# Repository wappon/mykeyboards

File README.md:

### wappon

e-mail:hetiantamo@gmail.com

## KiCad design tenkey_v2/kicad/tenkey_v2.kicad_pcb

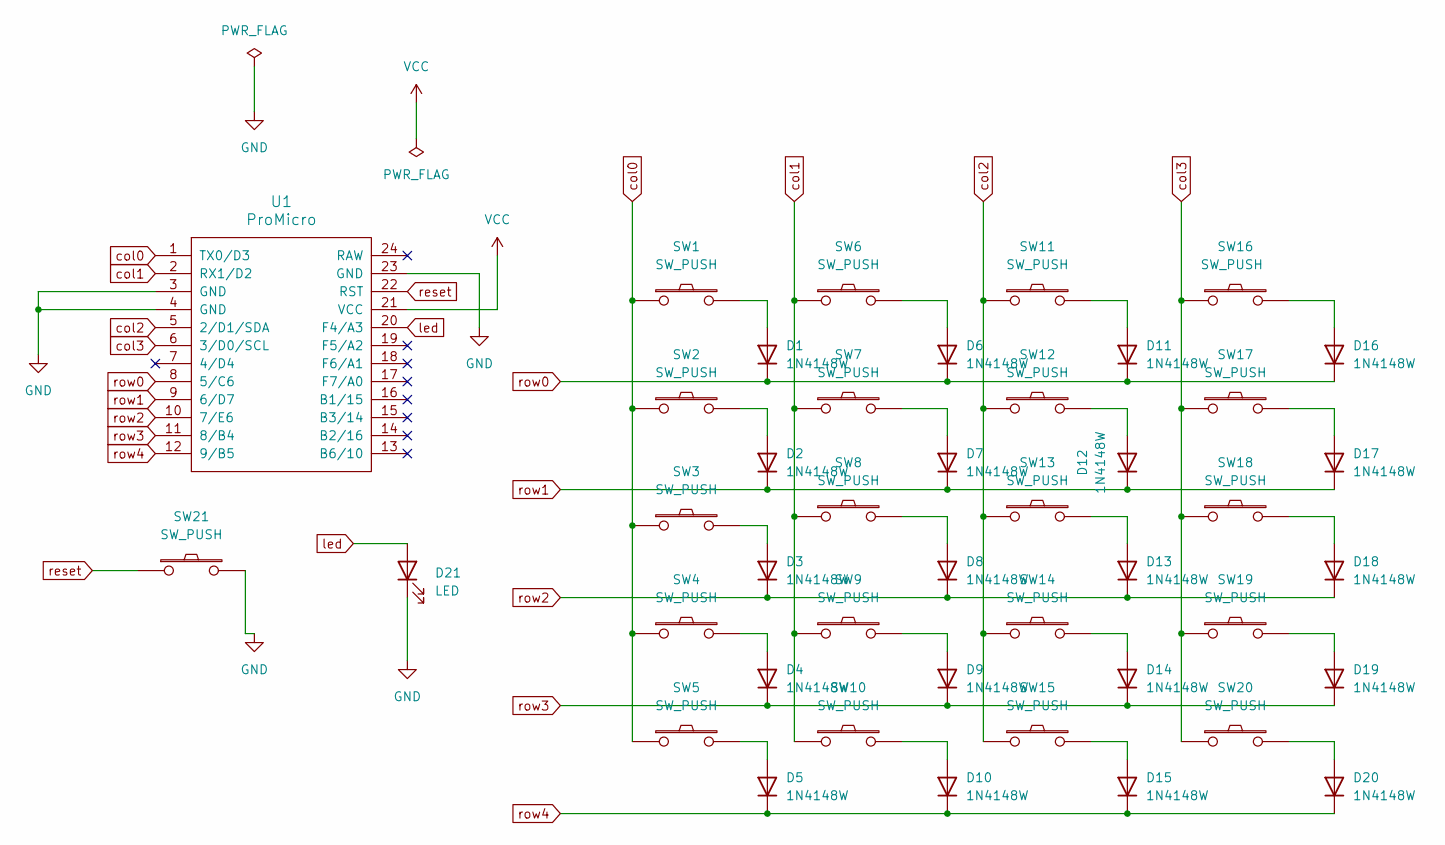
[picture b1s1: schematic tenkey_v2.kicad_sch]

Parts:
D1, D2, D3, D4, D5, D6, D7, D8, D9, D10, D11, D12, D13, D14, D15, D16, D17, D18, D19, D20: 1N4148W; D_SOD-123
D21: LED; LED_D3.0mm
SW1, SW2, SW3, SW4, SW5, SW6, SW7, SW8, SW9, SW10, SW11, SW12, SW13, SW14, SW15, SW16, SW17, SW18, SW19, SW20: SW_PUSH; SW_Cherry_MX_1.00u_PCB
SW21: SW_PUSH; ResetSW
U1: ProMicro; ArduinoProMicro

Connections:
GND: D21.1 (K), SW21.2, U1.3 (GND), U1.4 (GND), U1.23 (GND)
unnamed: D1.2 (A), SW1.2
unnamed: D2.2 (A), SW2.2
unnamed: D3.2 (A), SW3.2
unnamed: D4.2 (A), SW4.2
unnamed: D5.2 (A), SW5.2
unnamed: D6.2 (A), SW6.2
unnamed: D7.2 (A), SW7.2
unnamed: D8.2 (A), SW8.2
unnamed: D9.2 (A), SW9.2
unnamed: D10.2 (A), SW10.2
unnamed: D11.2 (A), SW11.2
unnamed: D12.2 (A), SW12.2
unnamed: D13.2 (A), SW13.2
unnamed: D14.2 (A), SW14.2
unnamed: D15.2 (A), SW15.2
unnamed: D16.2 (A), SW16.2
unnamed: D17.2 (A), SW17.2
unnamed: D18.2 (A), SW18.2
unnamed: D19.2 (A), SW19.2
unnamed: D20.2 (A), SW20.2
VCC: U1.21 (VCC)
col0: SW1.1, SW2.1, SW3.1, SW4.1, SW5.1, U1.1 (TX0/D3)
col1: SW6.1, SW7.1, SW8.1, SW9.1, SW10.1, U1.2 (RX1/D2)
col2: SW11.1, SW12.1, SW13.1, SW14.1, SW15.1, U1.5 (2/D1/SDA)
col3: SW16.1, SW17.1, SW18.1, SW19.1, SW20.1, U1.6 (3/D0/SCL)
led: D21.2 (A), U1.20 (F4/A3)
reset: SW21.1, U1.22 (RST)
row0: D1.1 (K), D6.1 (K), D11.1 (K), D16.1 (K), U1.8 (5/C6)
row1: D2.1 (K), D7.1 (K), D12.1 (K), D17.1 (K), U1.9 (6/D7)
row2: D3.1 (K), D8.1 (K), D13.1 (K), D18.1 (K), U1.10 (7/E6)
row3: D4.1 (K), D9.1 (K), D14.1 (K), D19.1 (K), U1.11 (8/B4)
row4: D5.1 (K), D10.1 (K), D15.1 (K), D20.1 (K), U1.12 (9/B5)

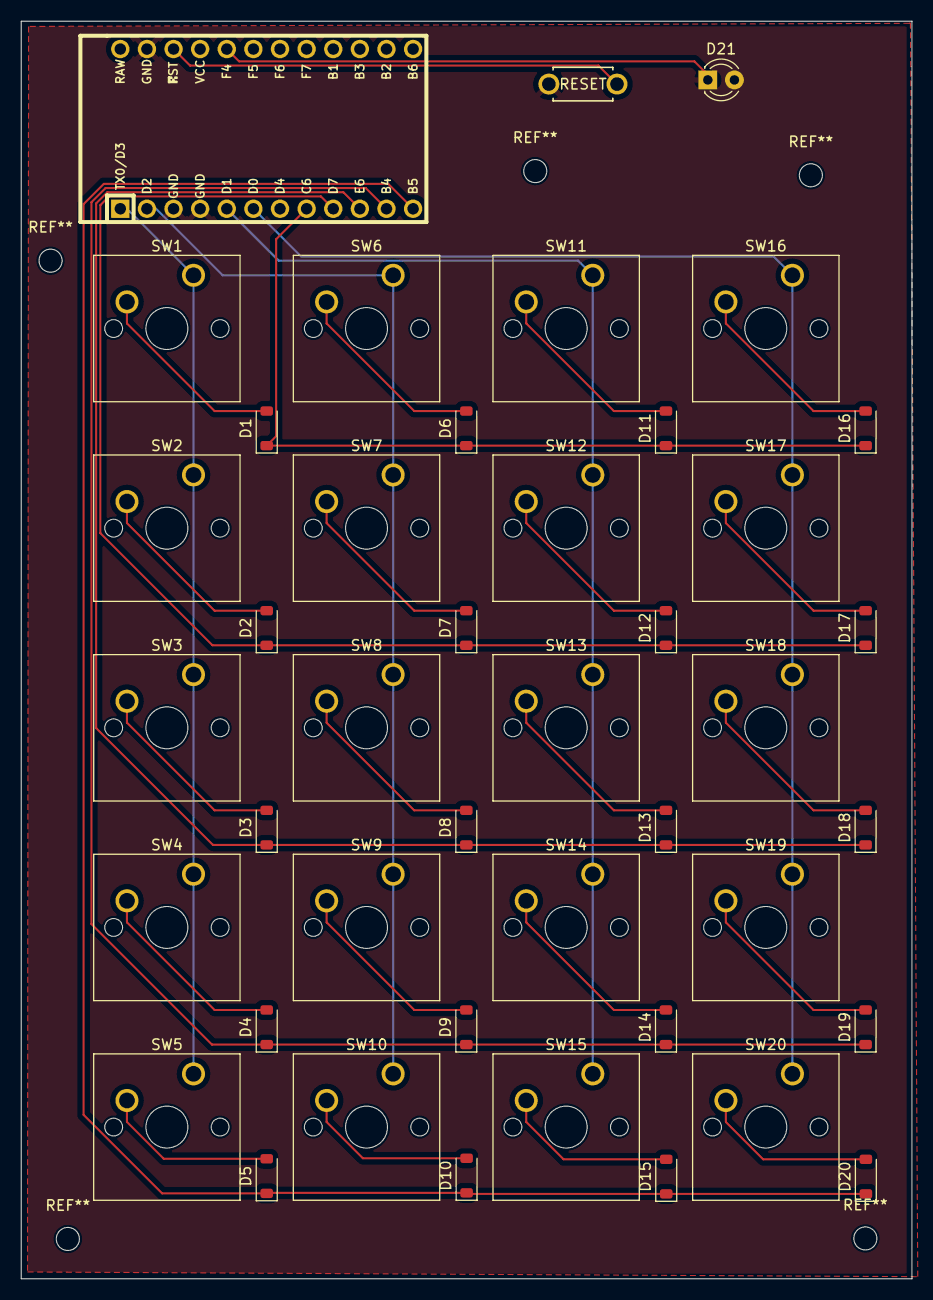
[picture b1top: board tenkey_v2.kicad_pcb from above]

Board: 2 copper layers, 85.0 x 120.0 mm, 43 parts (0 on the bottom side), 32 nets.

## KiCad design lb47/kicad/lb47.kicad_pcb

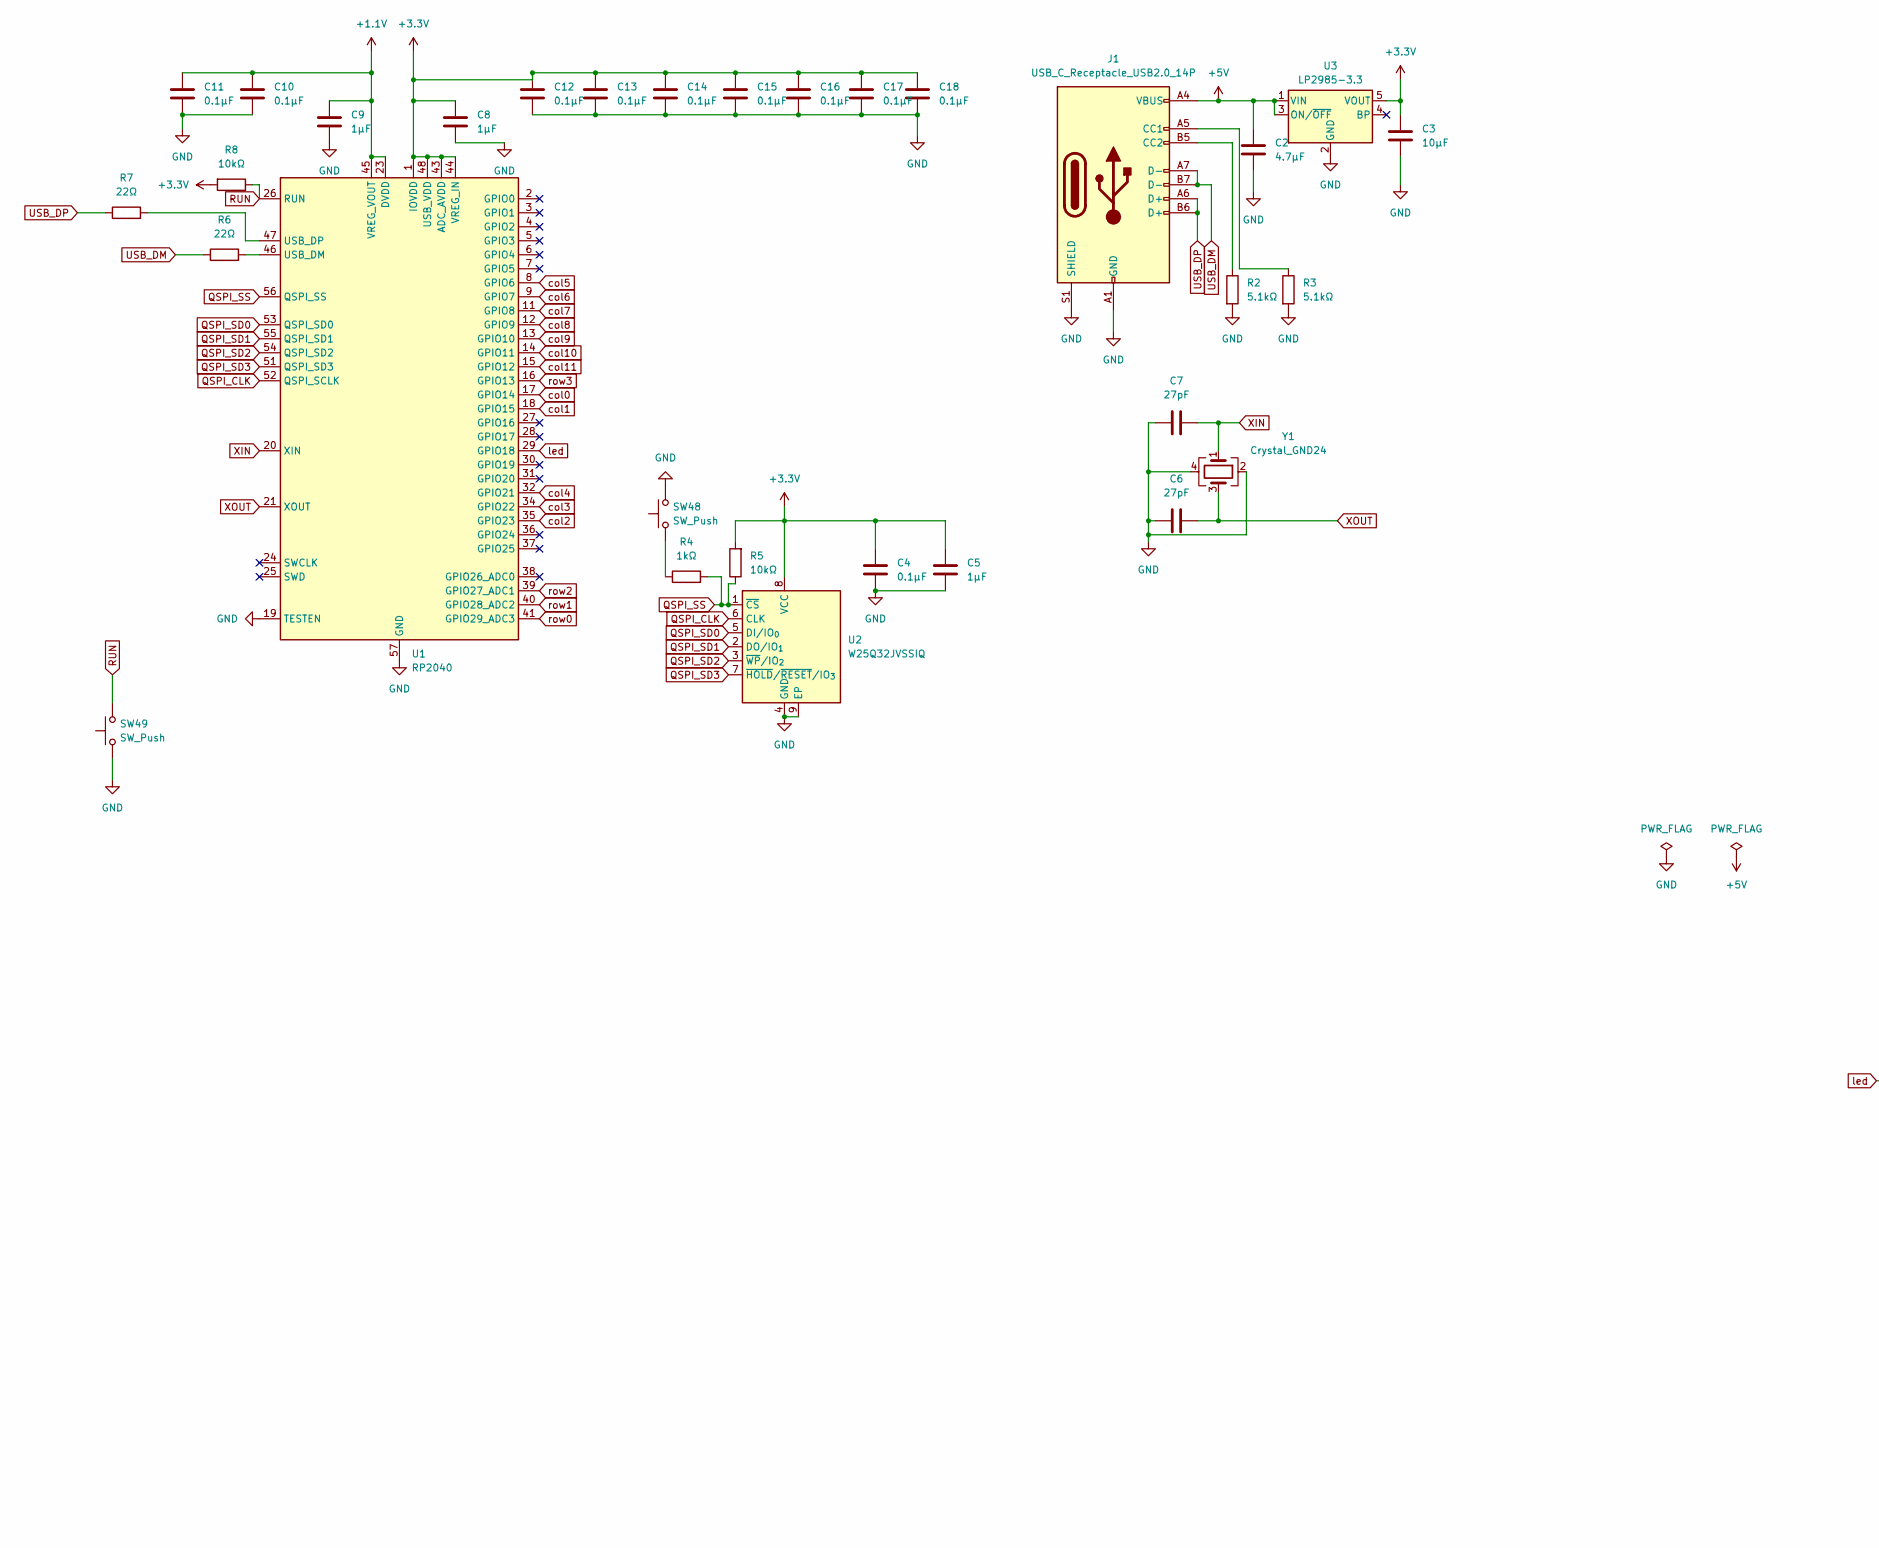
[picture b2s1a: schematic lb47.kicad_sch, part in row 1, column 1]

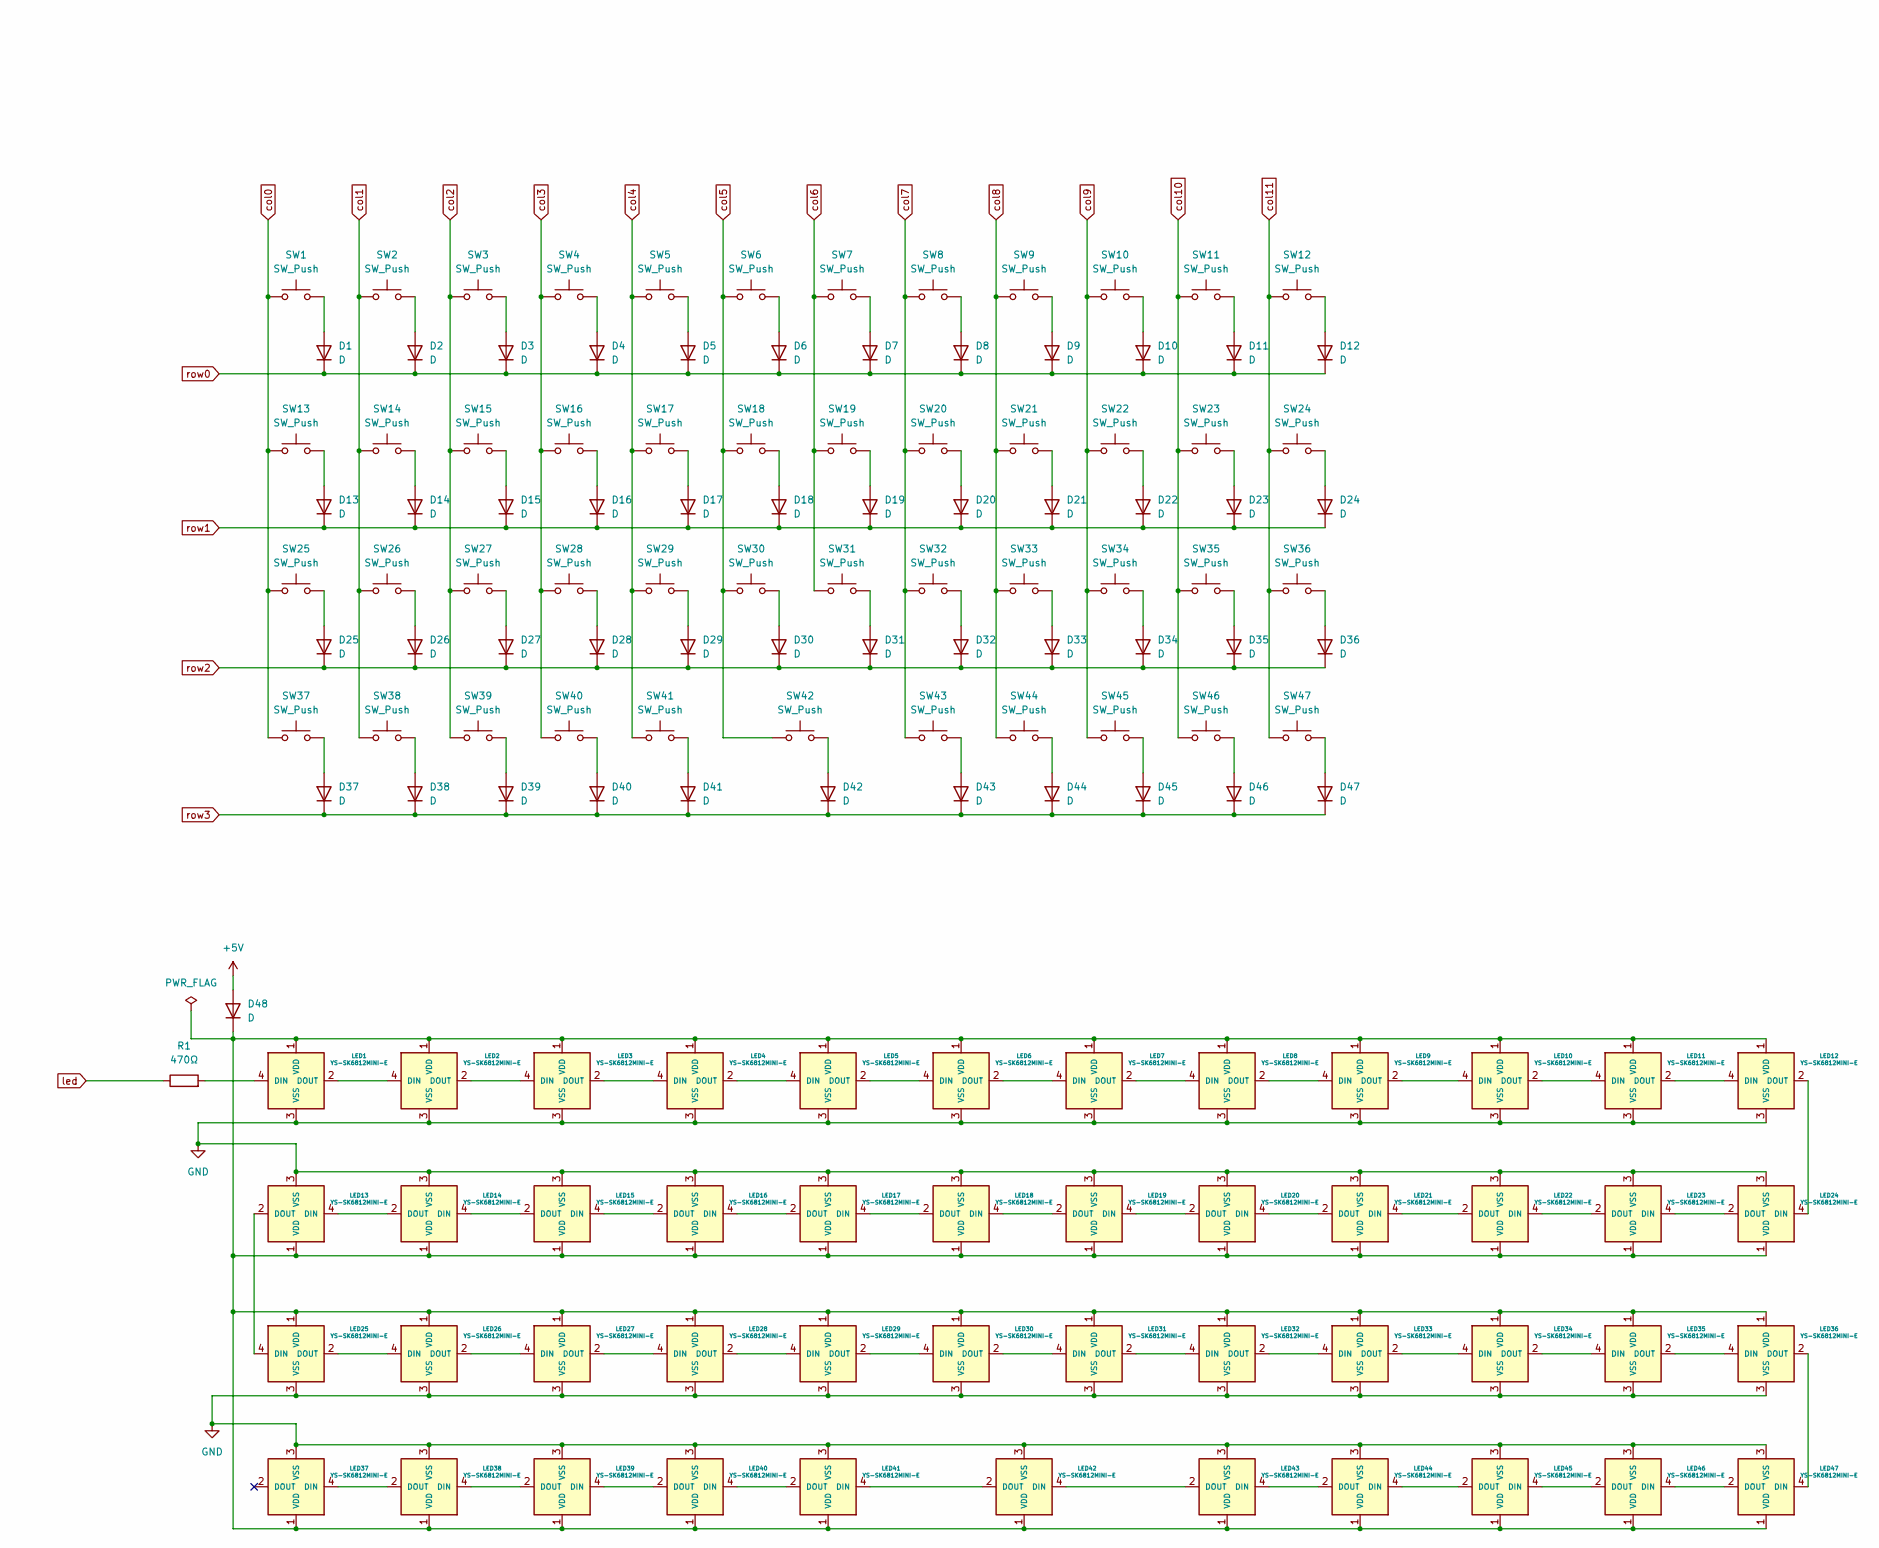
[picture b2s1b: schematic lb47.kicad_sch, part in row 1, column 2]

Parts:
C2: 4.7μF; C_0402_1005Metric; LCSC C335103
C3: 10μF; C_0402_1005Metric; LCSC C25054
C4, C10, C11, C12, C13, C14, C15, C16, C17, C18: 0.1μF; C_0402_1005Metric; LCSC C1525
C5, C8, C9: 1μF; C_0402_1005Metric; LCSC C14445
C6, C7: 27pF; C_0402_1005Metric; LCSC C1557
D1, D2, D3, D4, D5, D6, D7, D8, D9, D10, D11, D12, D13, D14, D15, D16, D17, D18, D19, D20, D21, D22, D23, D24, D25, D26, D27, D28, D29, D30, D31, D32, D33, D34, D35, D36, D37, D38, D39, D40, D41, D42, D43, D44, D45, D46, D47, D48: D; D_SOD-523; LCSC C27748
J1: USB_C_Receptacle_USB2.0_14P; USB_C_Receptacle_HRO_TYPE-C-31-M-12; LCSC C393939
LED1, LED2, LED3, LED4, LED5, LED6, LED7, LED8, LED9, LED10, LED11, LED12, LED13, LED14, LED15, LED16, LED17, LED18, LED19, LED20, LED21, LED22, LED23, LED24, LED25, LED26, LED27, LED28, LED29, LED30, LED31, LED32, LED33, LED34, LED35, LED36, LED37, LED38, LED39, LED40, LED41, LED42, LED43, LED44, LED45, LED46, LED47: YS-SK6812MINI-E; LCSC C5149201
R1: 470Ω; R_0402_1005Metric; LCSC C25117
R2, R3: 5.1kΩ; R_0402_1005Metric; LCSC C25905
R4: 1kΩ; R_0402_1005Metric; LCSC C11702
R5, R8: 10kΩ; R_0402_1005Metric; LCSC C25531
R6, R7: 22Ω; R_0402_1005Metric; LCSC C25092
SW1, SW2, SW3, SW4, SW5, SW6, SW7, SW8, SW9, SW10, SW11, SW12, SW13, SW14, SW15, SW16, SW17, SW18, SW19, SW20, SW21, SW22, SW23, SW24, SW25, SW26, SW27, SW28, SW29, SW30, SW31, SW32, SW33, SW34, SW35, SW36, SW37, SW38, SW39, SW40, SW41, SW42, SW43, SW44, SW45, SW46, SW47: SW_Push; CherryMX_Hotswap_1u
SW48, SW49: SW_Push; TSA017A2530B_C2888436; LCSC C589191
U1: RP2040; QFN-56-1EP_7x7mm_P0.4mm_EP3.2x3.2mm; LCSC C2040
U2: W25Q32JVSSIQ; WSON-8-1EP_8x6mm_P1.27mm_EP3.4x4.3mm; LCSC C82344
U3: LP2985-3.3; SOT-23-5; LCSC C95414
Y1: Crystal_GND24; Crystal_SMD_3225-4Pin_3.2x2.5mm; LCSC C403945

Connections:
+1.1V: C9.1, C10.1, C11.1, U1.23 (DVDD), U1.45 (VREG_VOUT), U1.50 (DVDD)
+3.3V: C3.1, C4.1, C5.1, C8.1, C12.1, C13.1, C14.1, C15.1, C16.1, C17.1, C18.1, R5.2, R8.2, U1.1 (IOVDD), U1.10 (IOVDD), U1.22 (IOVDD), U1.33 (IOVDD), U1.42 (IOVDD), U1.43 (ADC_AVDD), U1.44 (VREG_IN), U1.48 (USB_VDD), U1.49 (IOVDD), U2.8 (VCC), U3.5 (VOUT)
+5V: C2.1, D48.2 (A), J1.A4 (VBUS), J1.A9 (VBUS), J1.B4 (VBUS), J1.B9 (VBUS), U3.1 (VIN), U3.3 (ON/~OFF)
GND: C2.2, C3.2, C4.2, C5.2, C6.1, C7.1, C8.2, C9.2, C10.2, C11.2, C12.2, C13.2, C14.2, C15.2, C16.2, C17.2, C18.2, J1.A1 (GND), J1.A12 (GND), J1.B1 (GND), J1.B12 (GND), J1.S1 (SHIELD), LED1.3 (VSS), LED2.3 (VSS), LED3.3 (VSS), LED4.3 (VSS), LED5.3 (VSS), LED6.3 (VSS), LED7.3 (VSS), LED8.3 (VSS), LED9.3 (VSS), LED10.3 (VSS), LED11.3 (VSS), LED12.3 (VSS), LED13.3 (VSS), LED14.3 (VSS), LED15.3 (VSS), LED16.3 (VSS), LED17.3 (VSS), LED18.3 (VSS), LED19.3 (VSS), LED20.3 (VSS), LED21.3 (VSS), LED22.3 (VSS), LED23.3 (VSS), LED24.3 (VSS), LED25.3 (VSS), LED26.3 (VSS), LED27.3 (VSS), LED28.3 (VSS), LED29.3 (VSS), LED30.3 (VSS), LED31.3 (VSS), LED32.3 (VSS), LED33.3 (VSS), LED34.3 (VSS), LED35.3 (VSS), LED36.3 (VSS), LED37.3 (VSS), LED38.3 (VSS), LED39.3 (VSS), LED40.3 (VSS), LED41.3 (VSS), LED42.3 (VSS), LED43.3 (VSS), LED44.3 (VSS), LED45.3 (VSS), LED46.3 (VSS), LED47.3 (VSS), R2.2, R3.2, SW48.2, SW49.1, U1.19 (TESTEN), U1.57 (GND), U2.4 (GND), U2.9 (EP), U3.2 (GND), Y1.2, Y1.4
unnamed: D1.2 (A), SW1.2
unnamed: D2.2 (A), SW2.2
unnamed: D3.2 (A), SW3.2
unnamed: D4.2 (A), SW4.2
unnamed: D5.2 (A), SW5.2
unnamed: D6.2 (A), SW6.2
unnamed: D7.2 (A), SW7.2
unnamed: D8.2 (A), SW8.2
unnamed: D9.2 (A), SW9.2
unnamed: D10.2 (A), SW10.2
unnamed: D11.2 (A), SW11.2
unnamed: D12.2 (A), SW12.2
unnamed: D13.2 (A), SW13.2
unnamed: D14.2 (A), SW14.2
unnamed: D15.2 (A), SW15.2
unnamed: D16.2 (A), SW16.2
unnamed: D17.2 (A), SW17.2
unnamed: D18.2 (A), SW18.2
unnamed: D19.2 (A), SW19.2
unnamed: D20.2 (A), SW20.2
unnamed: D21.2 (A), SW21.2
unnamed: D22.2 (A), SW22.2
unnamed: D23.2 (A), SW23.2
unnamed: D24.2 (A), SW24.2
unnamed: D25.2 (A), SW25.2
unnamed: D26.2 (A), SW26.2
unnamed: D27.2 (A), SW27.2
unnamed: D28.2 (A), SW28.2
unnamed: D29.2 (A), SW29.2
unnamed: D30.2 (A), SW30.2
unnamed: D31.2 (A), SW31.2
unnamed: D32.2 (A), SW32.2
unnamed: D33.2 (A), SW33.2
unnamed: D34.2 (A), SW34.2
unnamed: D35.2 (A), SW35.2
unnamed: D36.2 (A), SW36.2
unnamed: D37.2 (A), SW37.2
unnamed: D38.2 (A), SW38.2
unnamed: D39.2 (A), SW39.2
unnamed: D40.2 (A), SW40.2
unnamed: D41.2 (A), SW41.2
unnamed: D42.2 (A), SW42.2
unnamed: D43.2 (A), SW43.2
unnamed: D44.2 (A), SW44.2
unnamed: D45.2 (A), SW45.2
unnamed: D46.2 (A), SW46.2
unnamed: D47.2 (A), SW47.2
unnamed: D48.1 (K), LED1.1 (VDD), LED2.1 (VDD), LED3.1 (VDD), LED4.1 (VDD), LED5.1 (VDD), LED6.1 (VDD), LED7.1 (VDD), LED8.1 (VDD), LED9.1 (VDD), LED10.1 (VDD), LED11.1 (VDD), LED12.1 (VDD), LED13.1 (VDD), LED14.1 (VDD), LED15.1 (VDD), LED16.1 (VDD), LED17.1 (VDD), LED18.1 (VDD), LED19.1 (VDD), LED20.1 (VDD), LED21.1 (VDD), LED22.1 (VDD), LED23.1 (VDD), LED24.1 (VDD), LED25.1 (VDD), LED26.1 (VDD), LED27.1 (VDD), LED28.1 (VDD), LED29.1 (VDD), LED30.1 (VDD), LED31.1 (VDD), LED32.1 (VDD), LED33.1 (VDD), LED34.1 (VDD), LED35.1 (VDD), LED36.1 (VDD), LED37.1 (VDD), LED38.1 (VDD), LED39.1 (VDD), LED40.1 (VDD), LED41.1 (VDD), LED42.1 (VDD), LED43.1 (VDD), LED44.1 (VDD), LED45.1 (VDD), LED46.1 (VDD), LED47.1 (VDD)
unnamed: J1.A5 (CC1), R3.1
unnamed: J1.B5 (CC2), R2.1
unnamed: LED1.4 (DIN), R1.2
unnamed: LED1.2 (DOUT), LED2.4 (DIN)
unnamed: LED2.2 (DOUT), LED3.4 (DIN)
unnamed: LED3.2 (DOUT), LED4.4 (DIN)
unnamed: LED4.2 (DOUT), LED5.4 (DIN)
unnamed: LED5.2 (DOUT), LED6.4 (DIN)
unnamed: LED6.2 (DOUT), LED7.4 (DIN)
unnamed: LED7.2 (DOUT), LED8.4 (DIN)
unnamed: LED8.2 (DOUT), LED9.4 (DIN)
unnamed: LED9.2 (DOUT), LED10.4 (DIN)
unnamed: LED10.2 (DOUT), LED11.4 (DIN)
unnamed: LED11.2 (DOUT), LED12.4 (DIN)
unnamed: LED12.2 (DOUT), LED24.4 (DIN)
unnamed: LED13.4 (DIN), LED14.2 (DOUT)
unnamed: LED13.2 (DOUT), LED25.4 (DIN)
unnamed: LED14.4 (DIN), LED15.2 (DOUT)
unnamed: LED15.4 (DIN), LED16.2 (DOUT)
unnamed: LED16.4 (DIN), LED17.2 (DOUT)
unnamed: LED17.4 (DIN), LED18.2 (DOUT)
unnamed: LED18.4 (DIN), LED19.2 (DOUT)
unnamed: LED19.4 (DIN), LED20.2 (DOUT)
unnamed: LED20.4 (DIN), LED21.2 (DOUT)
unnamed: LED21.4 (DIN), LED22.2 (DOUT)
unnamed: LED22.4 (DIN), LED23.2 (DOUT)
unnamed: LED23.4 (DIN), LED24.2 (DOUT)
unnamed: LED25.2 (DOUT), LED26.4 (DIN)
unnamed: LED26.2 (DOUT), LED27.4 (DIN)
unnamed: LED27.2 (DOUT), LED28.4 (DIN)
unnamed: LED28.2 (DOUT), LED29.4 (DIN)
unnamed: LED29.2 (DOUT), LED30.4 (DIN)
unnamed: LED30.2 (DOUT), LED31.4 (DIN)
unnamed: LED31.2 (DOUT), LED32.4 (DIN)
unnamed: LED32.2 (DOUT), LED33.4 (DIN)
unnamed: LED33.2 (DOUT), LED34.4 (DIN)
unnamed: LED34.2 (DOUT), LED35.4 (DIN)
unnamed: LED35.2 (DOUT), LED36.4 (DIN)
unnamed: LED36.2 (DOUT), LED47.4 (DIN)
unnamed: LED37.4 (DIN), LED38.2 (DOUT)
unnamed: LED38.4 (DIN), LED39.2 (DOUT)
unnamed: LED39.4 (DIN), LED40.2 (DOUT)
unnamed: LED40.4 (DIN), LED41.2 (DOUT)
unnamed: LED41.4 (DIN), LED42.2 (DOUT)
unnamed: LED42.4 (DIN), LED43.2 (DOUT)
unnamed: LED43.4 (DIN), LED44.2 (DOUT)
unnamed: LED44.4 (DIN), LED45.2 (DOUT)
unnamed: LED45.4 (DIN), LED46.2 (DOUT)
unnamed: LED46.4 (DIN), LED47.2 (DOUT)
unnamed: R4.1, SW48.1
unnamed: R6.2, U1.46 (USB_DM)
unnamed: R7.2, U1.47 (USB_DP)
QSPI_CLK: U1.52 (QSPI_SCLK), U2.6 (CLK)
QSPI_SD0: U1.53 (QSPI_SD0), U2.5 (DI/IO_{0})
QSPI_SD1: U1.55 (QSPI_SD1), U2.2 (DO/IO_{1})
QSPI_SD2: U1.54 (QSPI_SD2), U2.3 (~WP/IO_{2})
QSPI_SD3: U1.51 (QSPI_SD3), U2.7 (~HOLD/~RESET/IO_{3})
QSPI_SS: R4.2, R5.1, U1.56 (QSPI_SS), U2.1 (~CS)
RUN: R8.1, SW49.2, U1.26 (RUN)
USB_DM: J1.A7 (D-), J1.B7 (D-), R6.1
USB_DP: J1.A6 (D+), J1.B6 (D+), R7.1
XIN: C7.2, U1.20 (XIN), Y1.1
XOUT: C6.2, U1.21 (XOUT), Y1.3
col0: SW1.1, SW13.1, SW25.1, SW37.1, U1.17 (GPIO14)
col1: SW2.1, SW14.1, SW26.1, SW38.1, U1.18 (GPIO15)
col2: SW3.1, SW15.1, SW27.1, SW39.1, U1.35 (GPIO23)
col3: SW4.1, SW16.1, SW28.1, SW40.1, U1.34 (GPIO22)
col4: SW5.1, SW17.1, SW29.1, SW41.1, U1.32 (GPIO21)
col5: SW6.1, SW18.1, SW30.1, SW42.1, U1.8 (GPIO6)
col6: SW7.1, SW19.1, SW31.1, U1.9 (GPIO7)
col7: SW8.1, SW20.1, SW32.1, SW43.1, U1.11 (GPIO8)
col8: SW9.1, SW21.1, SW33.1, SW44.1, U1.12 (GPIO9)
col9: SW10.1, SW22.1, SW34.1, SW45.1, U1.13 (GPIO10)
col10: SW11.1, SW23.1, SW35.1, SW46.1, U1.14 (GPIO11)
col11: SW12.1, SW24.1, SW36.1, SW47.1, U1.15 (GPIO12)
led: R1.1, U1.29 (GPIO18)
row0: D1.1 (K), D2.1 (K), D3.1 (K), D4.1 (K), D5.1 (K), D6.1 (K), D7.1 (K), D8.1 (K), D9.1 (K), D10.1 (K), D11.1 (K), D12.1 (K), U1.41 (GPIO29_ADC3)
row1: D13.1 (K), D14.1 (K), D15.1 (K), D16.1 (K), D17.1 (K), D18.1 (K), D19.1 (K), D20.1 (K), D21.1 (K), D22.1 (K), D23.1 (K), D24.1 (K), U1.40 (GPIO28_ADC2)
row2: D25.1 (K), D26.1 (K), D27.1 (K), D28.1 (K), D29.1 (K), D30.1 (K), D31.1 (K), D32.1 (K), D33.1 (K), D34.1 (K), D35.1 (K), D36.1 (K), U1.39 (GPIO27_ADC1)
row3: D37.1 (K), D38.1 (K), D39.1 (K), D40.1 (K), D41.1 (K), D42.1 (K), D43.1 (K), D44.1 (K), D45.1 (K), D46.1 (K), D47.1 (K), U1.16 (GPIO13)

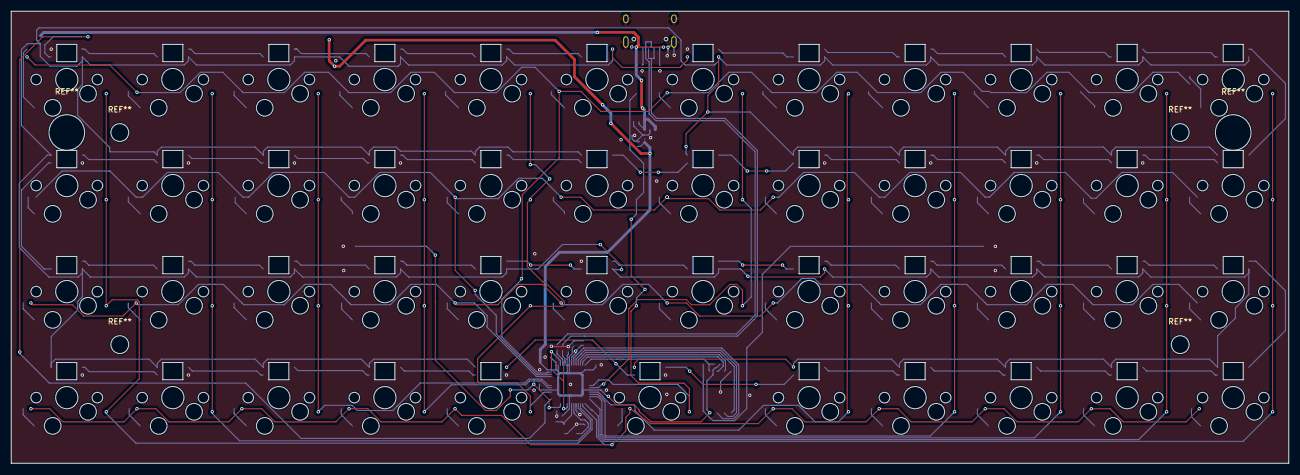
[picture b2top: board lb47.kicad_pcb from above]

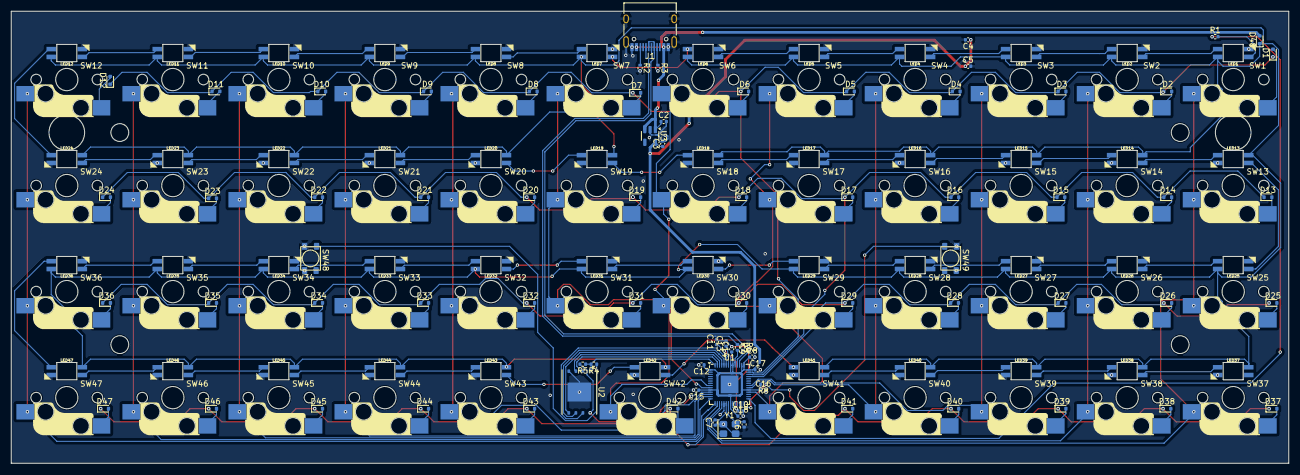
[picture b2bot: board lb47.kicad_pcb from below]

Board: 2 copper layers, 229.4 x 81.2 mm, 174 parts (127 on the bottom side), 132 nets.

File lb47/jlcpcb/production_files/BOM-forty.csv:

Comment,Designator,Footprint,LCSC,Quantity
1kΩ,R4,R_0402_1005Metric,C11702,1
1μF,"C5,C8,C9",C_0402_1005Metric,C14445,3
0.1μF,"C10,C11,C12,C13,C14,C15,C16,C17,C18,C4",C_0402_1005Metric,C1525,10
27pF,"C6,C7",C_0402_1005Metric,C1557,2
RP2040,U1,QFN-56-1EP_7x7mm_P0.4mm_EP3.2x3.2mm,C2040,1
4.7μF,C2,C_0402_1005Metric,C23687,1
22Ω,"R6,R7",R_0402_1005Metric,C25092,2
470Ω,R1,R_0402_1005Metric,C25117,1
10kΩ,"R5,R8",R_0402_1005Metric,C25531,2
5.1kΩ,"R2,R3",R_0402_1005Metric,C25905,2
D,"D1,D10,D11,D12,D13,D14,D15,D16,D17,D18,D19,D2,D20,D21,D22,D23,D24,D25,D26,D27,D28,D29,D3,D30,D31,D32,D33,D34,D35,D36,D37,D38,D39,D4,D40,D41,D42,D43,D44,D45,D46,D47,D48,D5,D6,D7,D8,D9",D_SOD-523,C27748,48
SW_Push,"SW48,SW49",TSA017A2530B_C2888436,C2888436,2
USB_C_Receptacle_USB2.0_14P,J1,USB_C_Receptacle_HRO_TYPE-C-31-M-12,C393939,1
Crystal_GND24,Y1,Crystal_SMD_3225-4Pin_3.2x2.5mm,C403945,1
YS-SK6812MINI-E,"LED1,LED10,LED11,LED12,LED13,LED14,LED15,LED16,LED17,LED18,LED19,LED2,LED20,LED21,LED22,LED23,LED24,LED25,LED26,LED27,LED28,LED29,LED3,LED30,LED31,LED32,LED33,LED34,LED35,LED36,LED37,LED38,LED39,LED4,LED40,LED41,LED42,LED43,LED44,LED45,LED46,LED47,LED5,LED6,LED7,LED8,LED9",YS-SK6812MINI-E,C5149201,47
10μF,C3,C_0402_1005Metric,C76991,1
W25Q32JVSSIQ,U2,WSON-8-1EP_8x6mm_P1.27mm_EP3.4x4.3mm,C82344,1
LP2985-3.3,U3,SOT-23-5,C95414,1

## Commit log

2025-09-22 update:lb47
2025-09-23 read.md追加
2025-09-23 fix: rename read.md to README.md
2025-09-23 tenkey_v3 case
2025-09-23 tenkey_v3 firmware
2025-09-23 fix:tenkey_v3
